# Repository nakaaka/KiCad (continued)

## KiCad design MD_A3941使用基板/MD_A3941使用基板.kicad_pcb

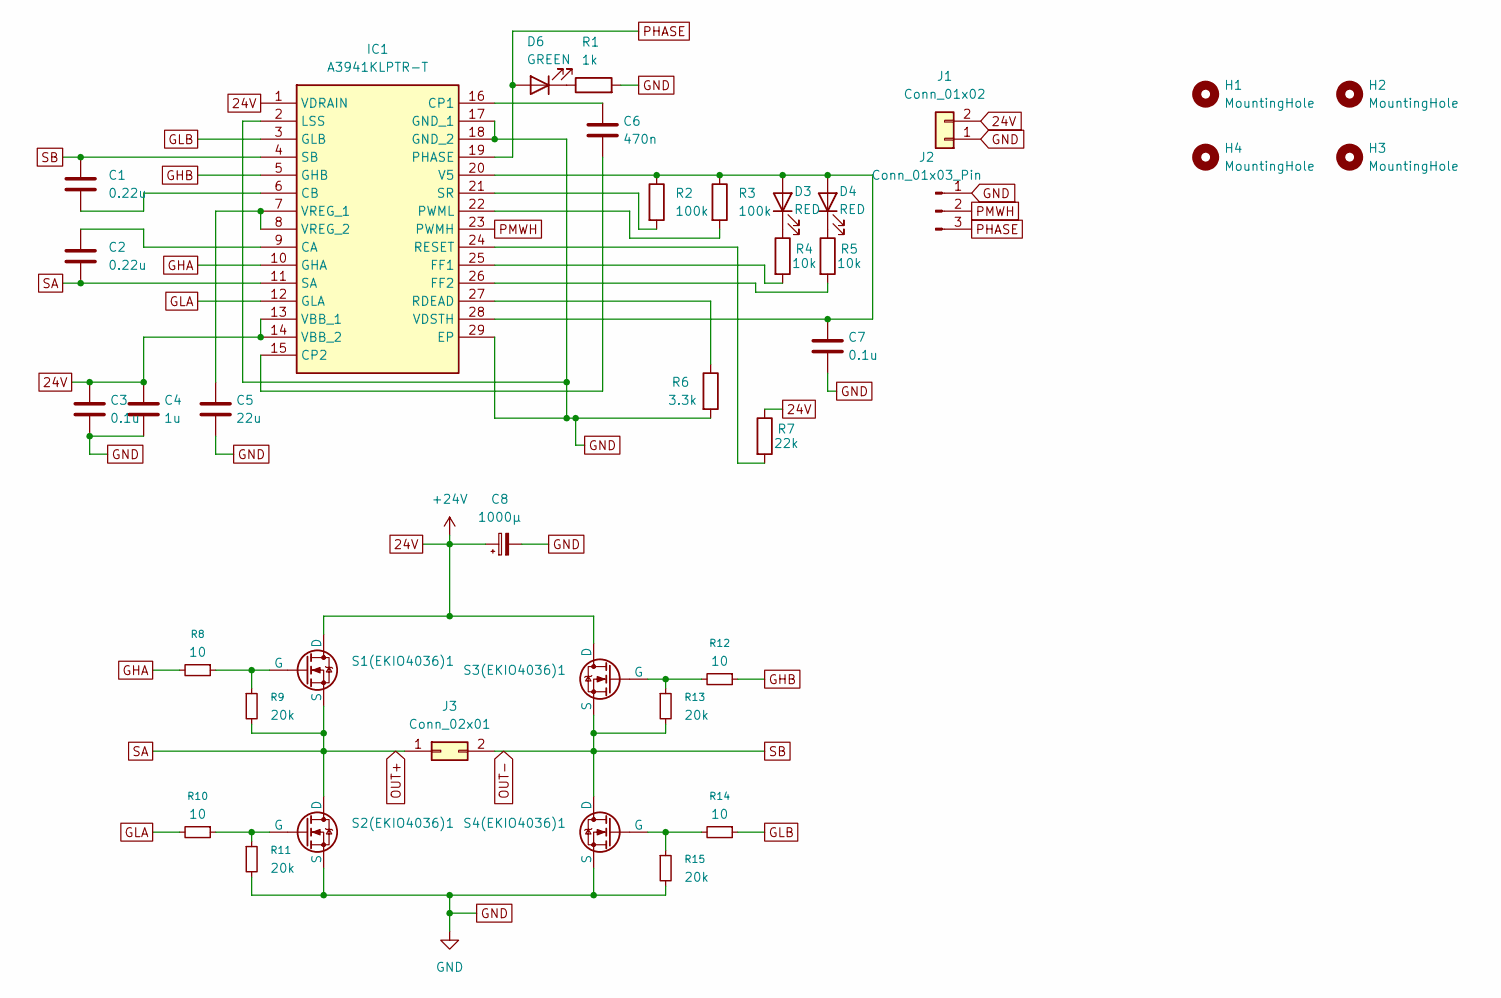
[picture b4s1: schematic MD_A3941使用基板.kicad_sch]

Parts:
C1, C2: 0.22u; C_0603_1608Metric
C3, C7: 0.1u; C_0603_1608Metric
C4: 1u; C_0603_1608Metric
C5: 22u; C_0603_1608Metric
C6: 470n; C_0603_1608Metric
C8: 1000μ; C_Radial_D12.5mm_H20.0mm_P5.00mm
D3, D4: RED; LED_0603_1608Metric
D6: GREEN; LED_0603_1608Metric
H1, H2, H3, H4: MountingHole; MountingHole_3.2mm_M3_Pad_Via
IC1: A3941KLPTR-T; A3941; Manufacturer_Part_Number A3941KLPTR-T
J1: Conn_01x02; AMASS_XT60PW-M_1x02_P7.20mm_Horizontal
J2: Conn_01x03_Pin; JST_XA_S03B-XASK-1_1x03_P2.50mm_Horizontal
J3: Conn_02x01; AMASS_XT60PW-M_1x02_P7.20mm_Horizontal
R1: 1k; R_0603_1608Metric
R2, R3: 100k; R_0603_1608Metric
R4, R5: 10k; R_0603_1608Metric
R6: 3.3k; R_0603_1608Metric
R7: 22k; R_0603_1608Metric
R8, R10, R12, R14: 10; R_0603_1608Metric
R9, R11, R13, R15: 20k; R_0603_1608Metric
S1(EKIO4036)1, S2(EKIO4036)1, S3(EKIO4036)1, S4(EKIO4036)1: NMOS; TO-220-3_Horizontal_TabUp

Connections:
24V: C3.1, C4.1, C8.1, IC1.1 (VDRAIN), IC1.13 (VBB_1), IC1.14 (VBB_2), J1.2, R7.1, S1(EKIO4036)1.1 (D), S3(EKIO4036)1.1 (D)
GHA: IC1.10 (GHA), R8.2
GHB: IC1.5 (GHB), R12.1
GLA: IC1.12 (GLA), R10.2
GLB: IC1.3 (GLB), R14.1
GND: C3.2, C4.2, C5.2, C7.2, C8.2, IC1.2 (LSS), IC1.17 (GND_1), IC1.18 (GND_2), IC1.29 (EP), J1.1, J2.1, R1.2, R6.2, R11.2, R15.2, S2(EKIO4036)1.3 (S), S4(EKIO4036)1.3 (S)
unnamed: C7.1, D3.2 (A), D4.2 (A), IC1.20 (V5), IC1.28 (VDSTH), R2.1, R3.1
unnamed: D3.1 (K), R4.1
unnamed: D4.1 (K), R5.1
unnamed: D6.1 (K), R1.1
unnamed: C2.1, IC1.9 (CA)
unnamed: C1.2, IC1.6 (CB)
unnamed: C6.1, IC1.16 (CP1)
unnamed: C6.2, IC1.15 (CP2)
unnamed: IC1.25 (FF1), R4.2
unnamed: IC1.26 (FF2), R5.2
unnamed: IC1.22 (PWML), R3.2
unnamed: IC1.27 (RDEAD), R6.1
unnamed: IC1.24 (RESET), R7.2
unnamed: IC1.21 (SR), R2.2
unnamed: C5.1, IC1.7 (VREG_1), IC1.8 (VREG_2)
unnamed: R8.1, R9.1, S1(EKIO4036)1.2 (G)
unnamed: R10.1, R11.1, S2(EKIO4036)1.2 (G)
unnamed: R12.2, R13.1, S3(EKIO4036)1.2 (G)
unnamed: R14.2, R15.1, S4(EKIO4036)1.2 (G)
OUT+: C2.2, IC1.11 (SA), J3.1, R9.2, S1(EKIO4036)1.3 (S), S2(EKIO4036)1.1 (D)
OUT-: C1.1, IC1.4 (SB), J3.2, R13.2, S3(EKIO4036)1.3 (S), S4(EKIO4036)1.1 (D)
PHASE: D6.2 (A), IC1.19 (PHASE), J2.3
PMWH: IC1.23 (PWMH), J2.2

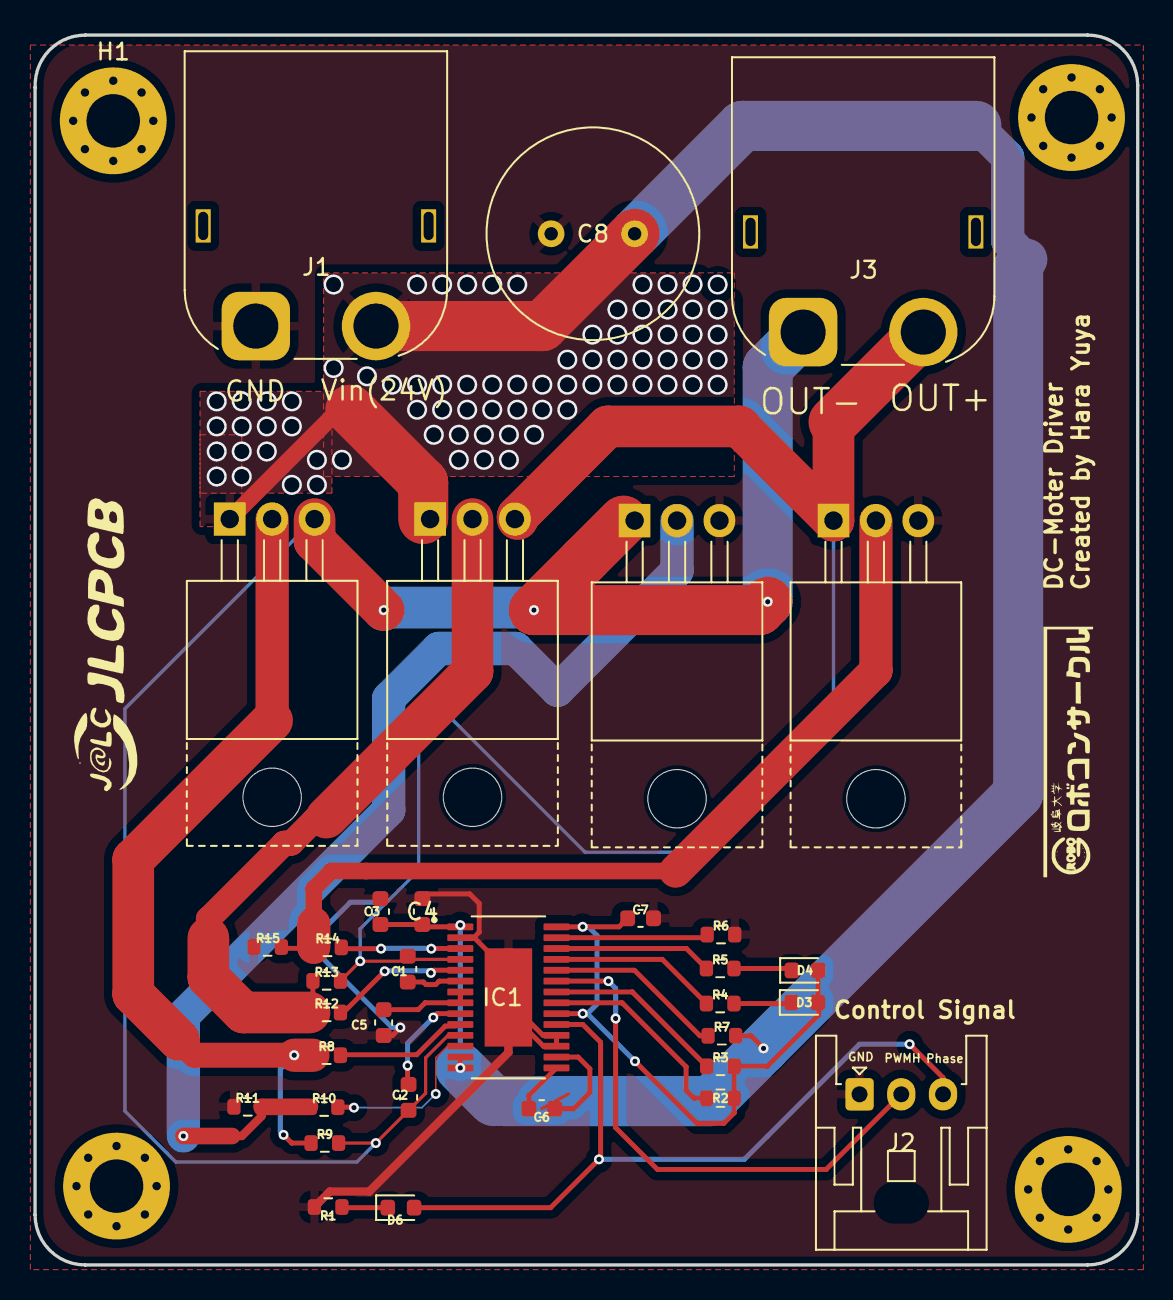
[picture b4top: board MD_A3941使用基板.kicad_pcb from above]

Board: 2 copper layers, 66.0 x 73.7 mm, 38 parts (0 on the bottom side), 29 nets.

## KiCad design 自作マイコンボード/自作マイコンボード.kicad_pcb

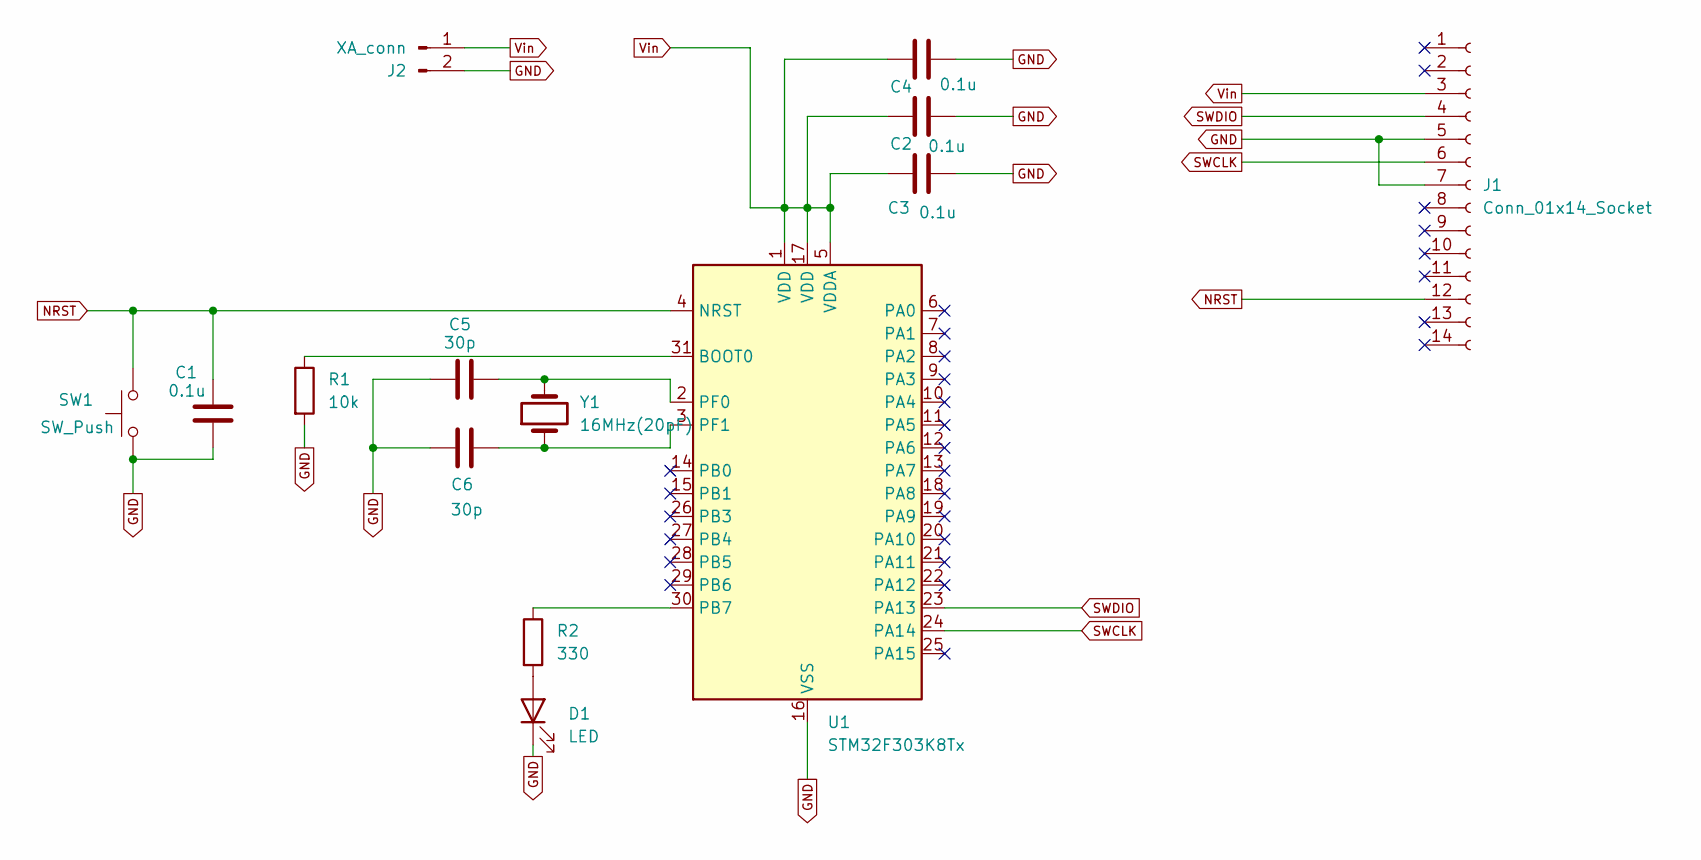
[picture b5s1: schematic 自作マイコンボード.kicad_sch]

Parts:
C1, C2, C3, C4: 0.1u; C_0603_1608Metric
C5, C6: 30p; C_0603_1608Metric
D1: LED; LED_0603_1608Metric
J1: Conn_01x14_Socket; 14pinコネクタ
J2: XA_conn; 2pinコネクタ
R1: 10k; R_0603_1608Metric
R2: 330; R_0603_1608Metric
SW1: SW_Push; SW_PUSH_6mm_H5mm
U1: STM32F303K8Tx; LQFP-32_7x7mm_P0.8mm
Y1: 16MHz(20pF); Crystal_HC49-4H_Vertical

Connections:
GND: C1.2, C2.2, C3.2, C4.2, C5.1, C6.1, D1.1 (K), J1.5, J1.7, J2.2, R1.2, SW1.1, U1.16 (VSS), U1.32 (VSS)
NRST: C1.1, J1.12, SW1.2, U1.4 (NRST)
unnamed: D1.2 (A), R2.2
unnamed: R1.1, U1.31 (BOOT0)
unnamed: R2.1, U1.30 (PB7)
unnamed: C5.2, U1.2 (PF0), Y1.2
unnamed: C6.2, U1.3 (PF1), Y1.1
SWCLK: J1.6, U1.24 (PA14)
SWDIO: J1.4, U1.23 (PA13)
Vin: C2.1, C3.1, C4.1, J1.3, J2.1, U1.1 (VDD), U1.5 (VDDA), U1.17 (VDD)

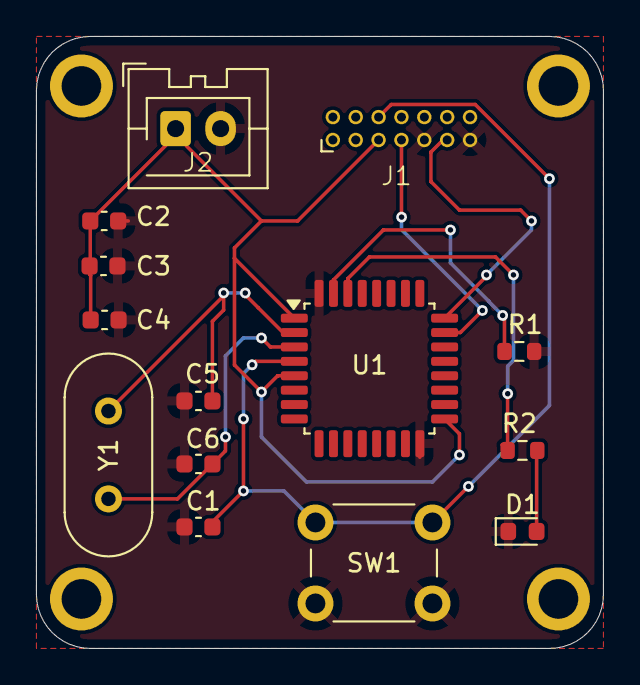
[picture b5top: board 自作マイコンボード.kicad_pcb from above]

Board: 2 copper layers, 31.5 x 34.0 mm, 14 parts (0 on the bottom side), 10 nets.

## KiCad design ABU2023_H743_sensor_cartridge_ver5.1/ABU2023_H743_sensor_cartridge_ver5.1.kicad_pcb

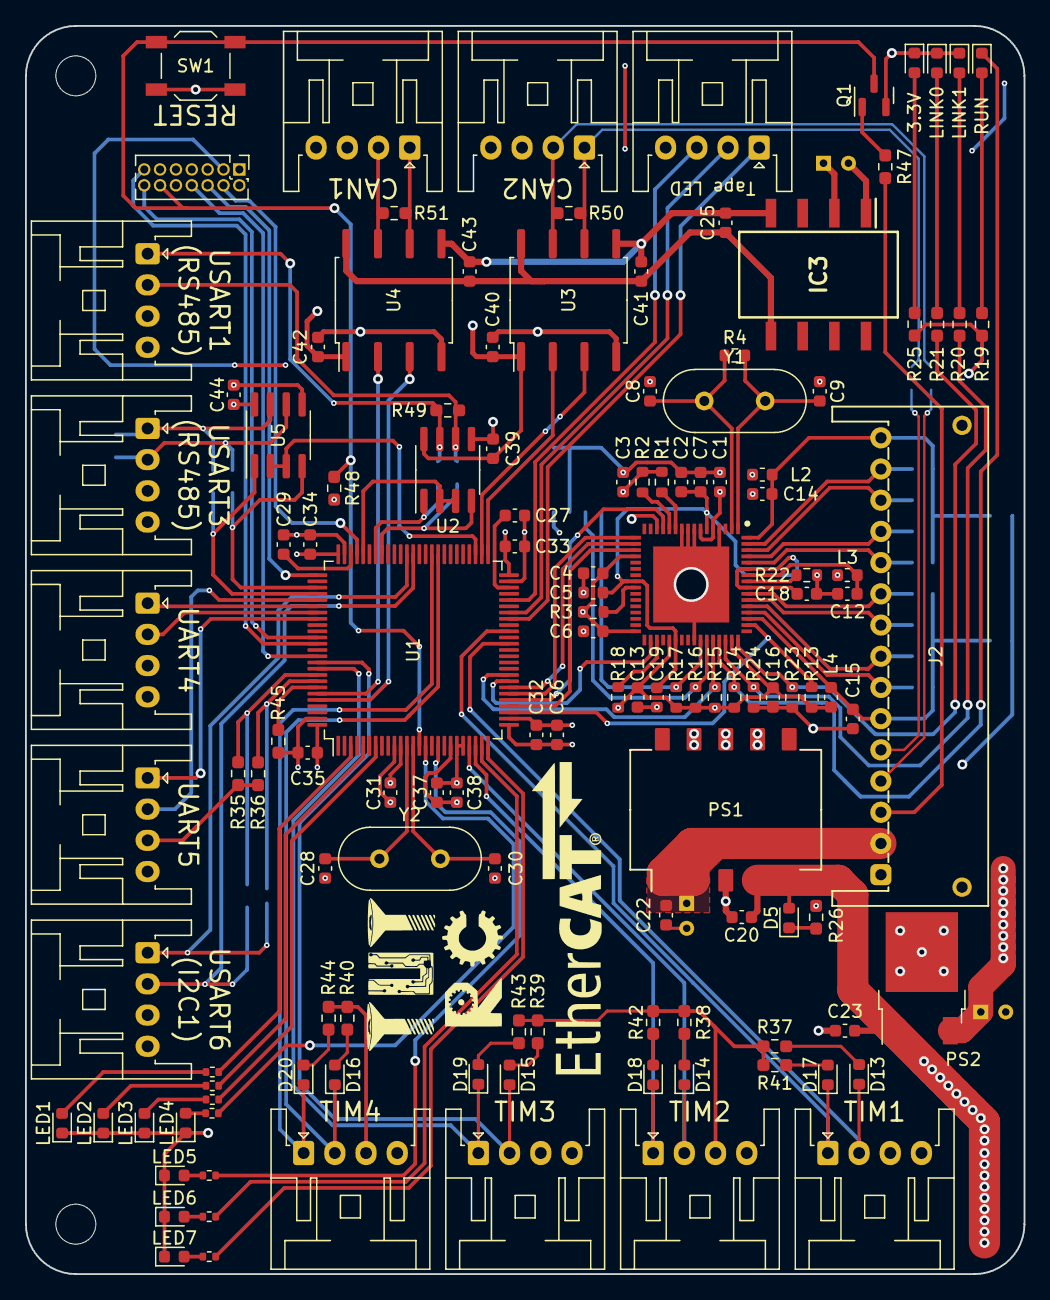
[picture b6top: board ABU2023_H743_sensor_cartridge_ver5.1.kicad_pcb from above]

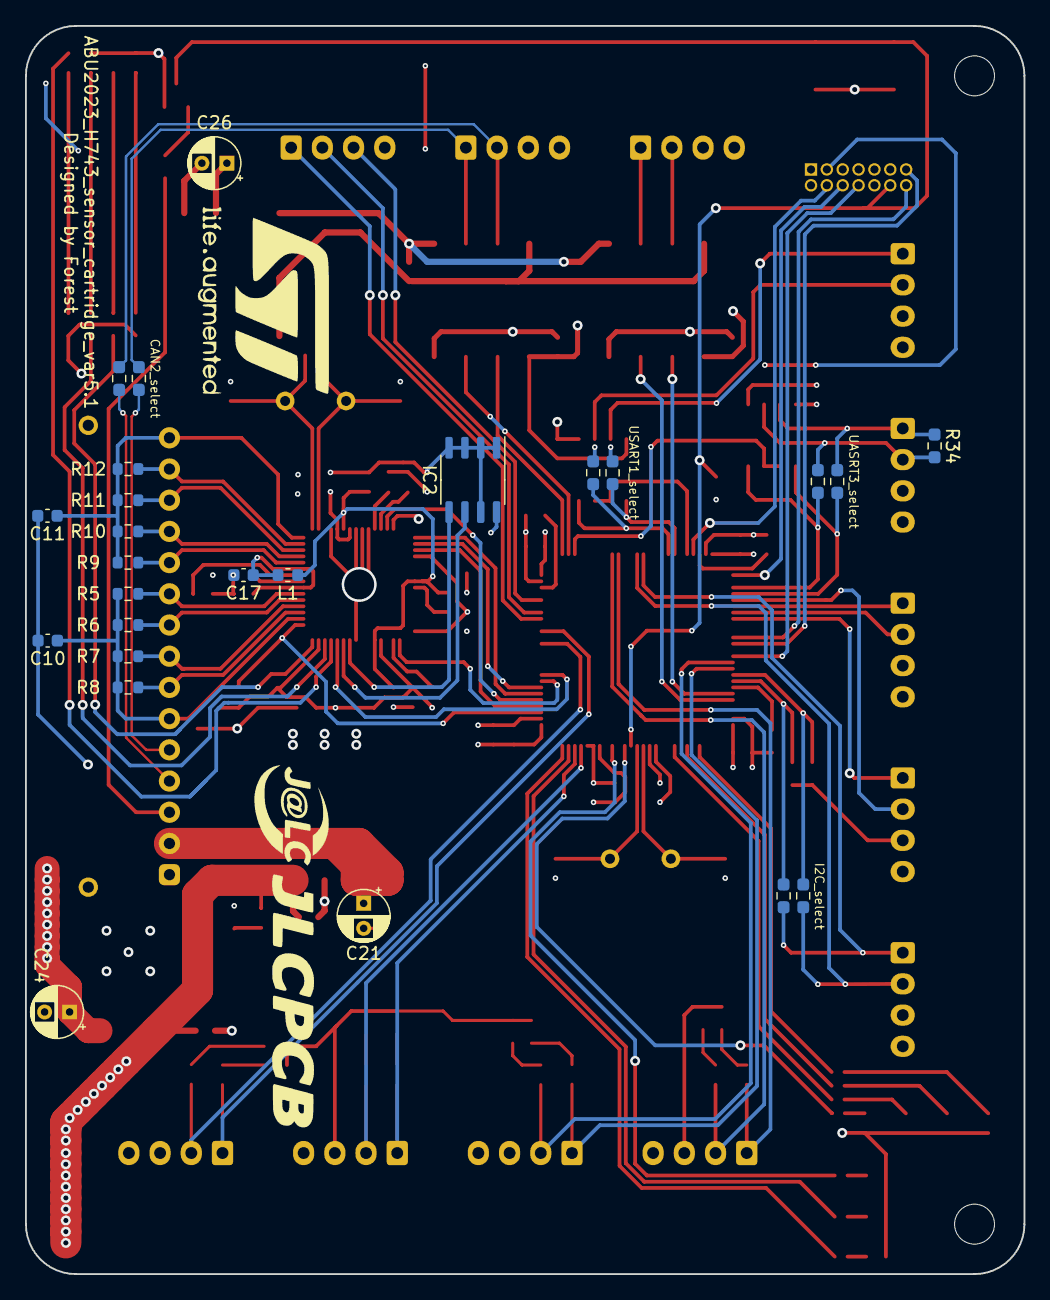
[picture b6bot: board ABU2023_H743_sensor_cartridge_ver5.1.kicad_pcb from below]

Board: 4 copper layers, 80.0 x 100.0 mm, 156 parts (25 on the bottom side), 117 nets.

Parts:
C1, C3, C4, C5, C6, C12, C13, C14, C15, C16, C17, C18, C19, C23, C31, C32, C33, C34, C35, C37, C39, C40, C41, C42, C43, C44: 0.1u; C_0603_1608Metric
C2: 420p; C_0603_1608Metric
C7, C38: 1u; C_0603_1608Metric
C8, C9: 33p; C_0603_1608Metric
C10, C11: 0,022u; C_0603_1608Metric
C20, C25, C36: 4.7u; C_0603_1608Metric
C21, C24: 47u; CP_Radial_D4.0mm_P2.00mm
C22, C27, C29: 2.2u; C_0603_1608Metric
C26: 4.7u; CP_Radial_D4.0mm_P2.00mm
C28, C30: 18p; C_0603_1608Metric
D1: RUNLED; LED_0603_1608Metric
D2: LINK1; LED_0603_1608Metric
D3: LINK0; LED_0603_1608Metric
D4: 3.3V; LED_0603_1608Metric
D5: 5V; LED_0603_1608Metric
D6, D7, D8, D9, D10, D11, D12: LED; LED_0603_1608Metric
D13, D14, D15, D16: LED_A; LED_0603_1608Metric
D17, D18, D19, D20: LED_B; LED_0603_1608Metric
IC1: LAN9253; QFN50P900X900X100-65N-D
IC2: 24FC512-I_P; SO-8_3.9x4.9mm_P1.27mm
IC3: VBT1-S5-S5-SMT; SOP254P1120X625-8N
J1: USART6; JST_XA_S04B-XASK-1_1x04_P2.50mm_Horizontal
J2: JL_01x15; JST_JL_S15B-JL-R
J3: UART4; JST_XA_S04B-XASK-1_1x04_P2.50mm_Horizontal
J4: UART5; JST_XA_S04B-XASK-1_1x04_P2.50mm_Horizontal
J5: UART3; JST_XA_S04B-XASK-1_1x04_P2.50mm_Horizontal
J6: UART1; JST_XA_S04B-XASK-1_1x04_P2.50mm_Horizontal
J7: CAN1; JST_XA_S04B-XASK-1_1x04_P2.50mm_Horizontal
J8: CAN2; JST_XA_S04B-XASK-1_1x04_P2.50mm_Horizontal
J9, J10, J11, J12: IncEncoder; JST_XA_S04B-XASK-1_1x04_P2.50mm_Horizontal
J13: TapeLED; JST_XA_S04B-XASK-1_1x04_P2.50mm_Horizontal
J14: STLINK-V3; STLINK-V3_THT
JP1, JP2, JP3, JP4, JP5, JP6, JP7, JP8: Jumper; R_0603_1608Metric_Pad0.98x0.95mm_HandSolder
L1, L2, L3, L4: 10m; L_0603_1608Metric
PS1: M78SAR05-0.5; M78SAR
PS2: NJM2391DL1-33; TO-252-2
Q1: 2N7002; SOT-23
R1, R2, R3, R13, R14, R15, R16, R17, R18, R23, R24: 4.7k; R_0603_1608Metric
R4: 1M; R_0603_1608Metric
R5, R6, R7, R8, R9, R10, R11, R12: 49.9; R_0603_1608Metric
R19, R20, R21, R25, R26, R35, R36, R37, R38, R39, R40, R41, R42, R43, R44, R48: 4.7k; R_0603_1608Metric_Pad0.98x0.95mm_HandSolder
R22: 12.1k; R_0603_1608Metric
R27, R28, R29, R30, R31, R32, R33: 4.7k; R_0402_1005Metric
R34, R49, R50, R51: 120; R_0603_1608Metric_Pad0.98x0.95mm_HandSolder
R45: 10k; R_0603_1608Metric_Pad0.98x0.95mm_HandSolder
R47: 1k; R_0603_1608Metric_Pad0.98x0.95mm_HandSolder
REF1, REF1#2: MountingHole_3.2mm_M3
SW1: SW_Push; SW_SPST_TL3342
U1: STM32H743VITx; LQFP-100_14x14mm_P0.5mm
U2, U5: MAX485E; SOIC-8_3.9x4.9mm_P1.27mm
U3, U4: ISO1050DUB; SOP-8_6.62x9.15mm_P2.54mm
Y1: 25MHz; Crystal_HC49-4H_Vertical
Y2: 32MHz; Crystal_HC49-4H_Vertical

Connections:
+1V2: C2.2, C5.2, C7.2, C19.1, IC1.6 (VDDCR_1), IC1.24 (VDDCR_2), IC1.38 (VDDCR_3), L1.1
+3V3: C1.2, C3.1, C4.2, C6.2, C13.1, C16.1, C24.1, C31.1, C32.1, C33.1, C34.1, C35.1, C36.1, C37.1, C38.1, IC1.5 (VDD33), IC1.7 (REG_EN), IC1.14 (VDDIO_1), IC1.20 (VDDIO_2), IC1.32 (VDDIO_3), IC1.37 (VDDIO_4), IC1.47 (VDDIO_5), IC2.8 (VCC), J14.3 (VDD), L2.1, L3.1, L4.1, PS2.3 (VOUT), R1.1, R2.1, R3.1, R13.2, R14.2, R15.2, R16.2, R17.2, R18.2, R19.1, R25.1, R48.1, U1.11 (VDD), U1.20 (VREF+), U1.21 (VDDA), U1.27 (VDD), U1.50 (VDD), U1.75 (VDD), U1.100 (VDD)
+5V: C20.1, C23.1, C26.1, C39.1, C40.2, C42.2, C44.1, D5.2 (A), IC3.2 (+VIN), J1.3, J3.3, J4.3, J5.3, J6.3, J9.3, J10.3, J11.3, J12.3, PS1.4 (Vout), PS1.5 (Vout), PS2.1 (VIN), R35.2, R36.2, R37.2, R38.2, R39.2, R40.2, R41.2, R42.2, R43.2, R44.2, U2.8 (VCC), U3.1 (VCC1), U4.1 (VCC1), U5.8 (VCC)
+5VA: C25.1, C41.2, C43.2, IC3.5 (+VO), U3.8 (VCC2), U4.8 (VCC2)
+12V: C21.1, C22.2, J2.2, J7.3, J8.3, PS1.1 (Vin), PS1.2 (Vin)
/CAN1_RX: U1.95 (PB8), U4.2 (RXD)
/CAN1_TX: U1.96 (PB9), U4.3 (TXD)
/CAN2_N: J8.1, JP7.2 (B), R50.2, U3.6 (CANL)
/CAN2_P: J8.2, JP8.2 (B), R50.1, U3.7 (CANH)
/CAN2_RX: U1.51 (PB12), U3.2 (RXD)
/CAN2_TX: U1.52 (PB13), U3.3 (TXD)
/I2C1_SCL: JP4.1 (A), R35.1, U1.92 (PB6)
/I2C1_SDA: JP3.1 (A), R36.1, U1.93 (PB7)
/IRQ: IC1.44 (IRQ/LATCH1), R15.1, U1.34 (PB0)
/ISO1050_1/CAN_H: J7.2, R51.1, U4.7 (CANH)
/ISO1050_1/CAN_L: J7.1, R51.2, U4.6 (CANL)
/LAN9253/RST#: IC1.11 (RST#), R1.2
/LAN9253/SCL: IC1.43 (EESCL/TCK/EE_EMUL2), IC2.6 (SCL), R16.1
/LAN9253/SDA: IC1.42 (EESDA/TMS/EE_EMUL1), IC2.5 (SDA), R17.1
/LAN9253/SIO2: IC1.12 (D2/AD2/SOF/SIO2/EE_EMUL_SPI0), R2.2
/LAN9253/SIO3: IC1.35 (D3/AD3/WD_TRIG/SIO3/EE_EMUL_SPI1), R18.1
/LED1: R27.1, U1.3 (PE4)
/LED2: R28.1, U1.5 (PE6)
/LED3: R29.1, U1.7 (PC13)
/LED4: R30.1, U1.15 (PC0)
/LED5: R31.1, U1.17 (PC2_C)
/LED6: R32.1, U1.24 (PA2)
/LED7: R33.1, U1.25 (PA3)
/LINKLED0: IC1.46 (LINKACTLED1/TDI/CHIP_MODE1/LEDPOL1), R20.1, R24.1
/LINKLED1: IC1.48 (LINKACTLED0/TDO/CHIP_MODE0/100FD_A/LEDP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), R21.1, R23.1
/MAX485E_1/A: J5.2, JP6.2 (B), R34.2, U5.6 (A)
/MAX485E_1/B: J5.1, JP5.2 (B), R34.1, U5.7 (B)
/MAX485E_2/A: J6.2, JP2.2 (B), R49.2, U2.6 (A)
/MAX485E_2/B: J6.1, JP1.2 (B), R49.1, U2.7 (B)
/RESET: J2.3, R47.1
/RUNLED: D1.1 (K), IC1.45 (RUNLED/STATE_RUNLED/E2PSIZE/EE_EMUL0/LE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), R14.1
/RXAN: IC1.54 (RXNA), J2.9, R6.2
/RXAP: IC1.55 (RXPA), J2.10, R5.1
/RXBN: IC1.61 (RXNB), J2.12, R10.2
/RXBP: IC1.60 (RXPB), J2.11, R9.1
/SCK: IC1.19 (D9/AD9/LATCH_IN/SCK), U1.29 (PA5)
/SIO0: IC1.17 (D0/AD0/WD_STATE/SI/SIO0), U1.31 (PA7)
/SIO1: IC1.13 (D1/AD1/EOF/SO/SIO1), U1.30 (PA6)
/SS: IC1.50 (D5/AD5/OUTVALID/SCS#), R13.1, U1.28 (PA4)
/STM32H743VGT6/NRST: J14.12 (NRST), Q1.3 (D), R48.2, SW1.2, U1.14 (NRST)
/STM32H743VGT6/SWCLK: J14.6 (SWCLK), U1.76 (PA14)
/STM32H743VGT6/SWDIO: J14.4 (SWDIO), U1.72 (PA13)
/STM32H743VGT6/SWO: J14.8 (SWO), U1.89 (PB3)
/STM32H743VGT6/VCP_Target_RX: J14.13 (STLINK_TX), U1.87 (PD6)
/STM32H743VGT6/VCP_Target_TX: J14.14 (STLINK_RX), U1.86 (PD5)
/SYNC0: IC1.34 (SYNC0/LATCH0/PME), U1.33 (PC5)
/SYNC1: IC1.18 (SYNC1/LATCH1/PME), U1.32 (PC4)
/TIM1_CH1: D13.1 (K), J9.2, U1.39 (PE9)
/TIM1_CH2: D17.1 (K), J9.1, U1.41 (PE11)
/TIM2_CH1: D14.1 (K), J10.2, U1.22 (PA0)
/TIM2_CH2: D18.1 (K), J10.1, U1.23 (PA1)
/TIM3_CH1: D15.1 (K), J11.2, U1.90 (PB4)
/TIM3_CH2: D19.1 (K), J11.1, U1.91 (PB5)
/TIM4_CH1: D16.1 (K), J12.2, U1.59 (PD12)
/TIM4_CH2: D20.1 (K), J12.1, U1.60 (PD13)
/TXAN: IC1.52 (TXNA), J2.7, R8.2
/TXAP: IC1.53 (TXPA), J2.8, R7.1
/TXBN: IC1.63 (TXNB), J2.14, R12.2
/TXBP: IC1.62 (TXPB), J2.13, R11.1
/TapeLED_B: J13.3, U1.46 (PB10)
/TapeLED_G: J13.2, U1.44 (PE14)
/TapeLED_R: J13.1, U1.43 (PE13)
/UART4_RX: J3.1, U1.81 (PD0)
/UART4_TX: J3.2, U1.82 (PD1)
/UART5_RX: J4.1, U1.83 (PD2)
/UART5_TX: J4.2, U1.80 (PC12)
/USART1_DE: U1.71 (PA12), U2.2 (~RE), U2.3 (DE)
/USART1_RX: JP1.1 (A), U1.69 (PA10), U2.1 (RO)
/USART1_TX: JP2.1 (A), U1.68 (PA9), U2.4 (DI)
/USART3_DE: U1.53 (PB14), U5.2 (~RE), U5.3 (DE)
/USART3_RX: JP5.1 (A), U1.79 (PC11), U5.1 (RO)
/USART3_TX: JP6.1 (A), U1.78 (PC10), U5.4 (DI)
/USART6_RX: J1.1, JP3.2 (B), U1.64 (PC7)
/USART6_TX: J1.2, JP4.2 (B), U1.63 (PC6)
/VDD33TXRX1: C10.1, C15.1, IC1.51 (VDD33TXRX1), J2.6, L4.2, R5.2, R6.1, R7.2, R8.1
/VDD33TXRX2: C11.1, C14.1, IC1.64 (VDD33TXRX2), J2.15, L2.2, R9.2, R10.1, R11.2, R12.1
GND: C1.1, C2.1, C3.2, C4.1, C5.1, C6.1, C7.1, C8.1, C9.1, C10.2, C11.2, C12.2, C13.2, C14.2, C15.2, C16.2, C17.2, C18.2, C19.2, C20.2, C21.2, C22.1, C23.2, C24.2, C26.2, C27.2, C28.2, C29.2, C30.2, C31.2, C32.2, C33.2, C34.2, C35.2, C36.2, C37.2, C38.2, C39.2, C40.1, C42.1, C44.2, D2.1 (K), D3.1 (K), D4.1 (K), D6.1 (K), D7.1 (K), D8.1 (K), D9.1 (K), D10.1 (K), D11.1 (K), D12.1 (K), IC1.4 (OSCVSS), IC1.8 (CLK_25/CLK_25_EN/XTAL_MODE), IC1.9 (ERRLED/PME/100FD_B/LEDPOL4), IC1.10 (WAIT_ACK/PME/LATCH0//EE_EMUL_SPI3), IC1.41 (TESTMODE), IC1.65 (VSS), IC2.1 (A0), IC2.2 (A1), IC2.3 (A2), IC2.4 (VSS), IC2.7 (WP), IC3.1 (GND), J1.4, J2.1, J3.4, J4.4, J5.4, J6.4, J7.4, J8.4, J9.4, J10.4, J11.4, J12.4, J13.4, J14.5 (VSS), J14.7 (VSS), PS1.3 (GND), PS1.7 (GND), PS1.8 (GND)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
GNDA: C25.2, C41.1, C43.1, IC3.4 (0_V), U3.5 (GND2), U4.5 (GND2)
unnamed: D1.2 (A), R19.2
unnamed: D2.2 (A), R20.2
unnamed: D3.2 (A), R21.2
unnamed: D4.2 (A), R25.2
unnamed: D5.1 (K), R26.1
unnamed: D6.2 (A), R27.2
unnamed: D7.2 (A), R28.2
unnamed: D8.2 (A), R29.2
unnamed: D9.2 (A), R30.2
unnamed: D10.2 (A), R31.2
unnamed: D11.2 (A), R32.2
unnamed: D12.2 (A), R33.2
unnamed: D13.2 (A), R37.1
unnamed: D14.2 (A), R38.1
unnamed: D15.2 (A), R39.1
unnamed: D16.2 (A), R40.1
unnamed: D17.2 (A), R41.1
unnamed: D18.2 (A), R42.1
unnamed: D19.2 (A), R43.1
unnamed: D20.2 (A), R44.1
unnamed: IC1.25 (A1/ALELO/OE_EXT/MII_CLK25//EE_EMUL_SPI2), R3.2
unnamed: C9.2, IC1.1 (OSCI), R4.2, Y1.2
unnamed: C8.2, IC1.2 (OSCO), R4.1, Y1.1
unnamed: IC1.57 (RBIAS), R22.1
unnamed: C17.1, C18.1, IC1.56 (VDD12TX1), IC1.59 (VDD12TX2), L1.2
unnamed: C12.1, IC1.58 (VDD33BIAS), L3.2
unnamed: J2.4, JP8.1 (A)
unnamed: J2.5, JP7.1 (A)
unnamed: Q1.1 (G), R47.2
unnamed: R45.2, U1.94 (BOOT0)
unnamed: C28.1, U1.12 (PH0), Y2.1
unnamed: C30.1, U1.13 (PH1), Y2.2
unnamed: C27.1, U1.48 (VCAP1)
unnamed: C29.1, U1.73 (VCAP2)

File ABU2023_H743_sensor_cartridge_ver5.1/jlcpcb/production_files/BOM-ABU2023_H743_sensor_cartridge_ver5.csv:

Comment,Designator,Footprint,LCSC
STM32H743VITx,U1,LQFP-100_14x14mm_P0.5mm,C114409
0.1u,"C1,C12,C13,C14,C15,C16,C17,C18,C19,C23,C3,C31,C32,C33,C34,C35,C37,C39,C4,C40,C41,C42,C43,C44,C5,C6",C_0603_1608Metric,C14663
1u,"C38,C7",C_0603_1608Metric,C15849
ISO1050DUB,"U3,U4",SOP-8_6.62x9.15mm_P2.54mm,C16428
18p,"C28,C30",C_0603_1608Metric,C1647
33p,"C8,C9",C_0603_1608Metric,C1663
4.7u,"C20,C25,C36",C_0603_1608Metric,C19666
"0,022u","C10,C11",C_0603_1608Metric,C21122
1k,R47,R_0603_1608Metric_Pad0.98x0.95mm_HandSolder,C21190
120,"R34,R49,R50,R51",R_0603_1608Metric_Pad0.98x0.95mm_HandSolder,C22787
5V,D5,LED_0603_1608Metric,C2286
LED,"D11,D7,D9",LED_0603_1608Metric,C2290
1M,R4,R_0603_1608Metric,C22935
4.7k,"R1,R13,R14,R15,R16,R17,R18,R19,R2,R20,R21,R23,R24,R25,R26,R3,R35,R36,R37,R38,R39,R40,R41,R42,R43,R44,R48",R_0603_1608Metric,C23162
49.9,"R10,R11,R12,R5,R6,R7,R8,R9",R_0603_1608Metric,C23185
2.2u,"C22,C27,C29",C_0603_1608Metric,C23630
10k,R45,R_0603_1608Metric_Pad0.98x0.95mm_HandSolder,C25804
4.7k,"R27,R28,R29,R30,R31,R32,R33",R_0402_1005Metric,C25900
USART6,"J1,J10,J11,J12,J13,J3,J4,J5,J6,J7,J8,J9",JST_XA_S04B-XASK-1_1x04_P2.50mm_Horizontal,C265097
SW_Push,SW1,SW_SPST_TL3342,C318884
MAX485E,"U2,U5",SOIC-8_3.9x4.9mm_P1.27mm,C6855
12.1k,R22,R_0603_1608Metric,C705893
RUNLED,"D1,D10,D12,D6,D8",LED_0603_1608Metric,C72038
LED_B,"D17,D18,D19,D2,D20,D3",LED_0603_1608Metric,C72041
LED_A,"D13,D14,D15,D16,D4",LED_0603_1608Metric,C72043
2N7002,Q1,SOT-23,C8545
10m,"L1,L2,L3,L4",L_0603_1608Metric,C85827
Jumper,JP6,R_0603_1608Metric_Pad0.98x0.95mm_HandSolder,
Jumper,JP8,R_0603_1608Metric_Pad0.98x0.95mm_HandSolder,
Jumper,JP7,R_0603_1608Metric_Pad0.98x0.95mm_HandSolder,
Jumper,JP5,R_0603_1608Metric_Pad0.98x0.95mm_HandSolder,
Jumper,JP4,R_0603_1608Metric_Pad0.98x0.95mm_HandSolder,
Jumper,JP3,R_0603_1608Metric_Pad0.98x0.95mm_HandSolder,
Jumper,JP2,R_0603_1608Metric_Pad0.98x0.95mm_HandSolder,
Jumper,JP1,R_0603_1608Metric_Pad0.98x0.95mm_HandSolder,
32MHz,Y2,Crystal_HC49-4H_Vertical,
M78SAR05-0.5,PS1,M78SAR,
NJM2391DL1-33,PS2,TO-252-2,
420p,C2,C_0603_1608Metric,
25MHz,Y1,Crystal_HC49-4H_Vertical,
JL_01x15,J2,JST_JL_S15B-JL-R,
STLINK-V3,J14,STLINK-V3_THT,
VBT1-S5-S5-SMT,IC3,SOP254P1120X625-8N,
LAN9253,IC1,QFN50P900X900X100-65N-D,
47u,C24,CP_Radial_D4.0mm_P2.00mm,
47u,C21,CP_Radial_D4.0mm_P2.00mm,
24FC512-I_P,IC2,SO-8_3.9x4.9mm_P1.27mm,
4.7u,C26,CP_Radial_D4.0mm_P2.00mm,

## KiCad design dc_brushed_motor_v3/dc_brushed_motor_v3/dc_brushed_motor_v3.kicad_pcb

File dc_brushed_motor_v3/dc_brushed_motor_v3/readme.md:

ブラシ付きモータードライバーの制作
堀江　新

回路設計は原と堀江で行った。

---- メモ ----
mosfetは複数の企業が販売しているが、大きさは規格化されている。(例　TO220)
　　(レギュレータなども同規格で表されることが多い)

表面実装はSMD、スルーホールはTHTで表される

スルーホールの部品の足を切って、基盤に表面実装することをリードフォーミングという
stagger_odd とstagger_evenについて
　　リードの曲げ方。
　　stagger_oddは奇数を曲げる
　　stagger_evenは偶数番目で曲げる
　　ショートしにくいのはstagger_even

基本的に、スルーホールのfetであれば、リードにはんだ付けする
タブはドレインになっていることが多いが、放熱用なので、基盤にねじ固定することが主流

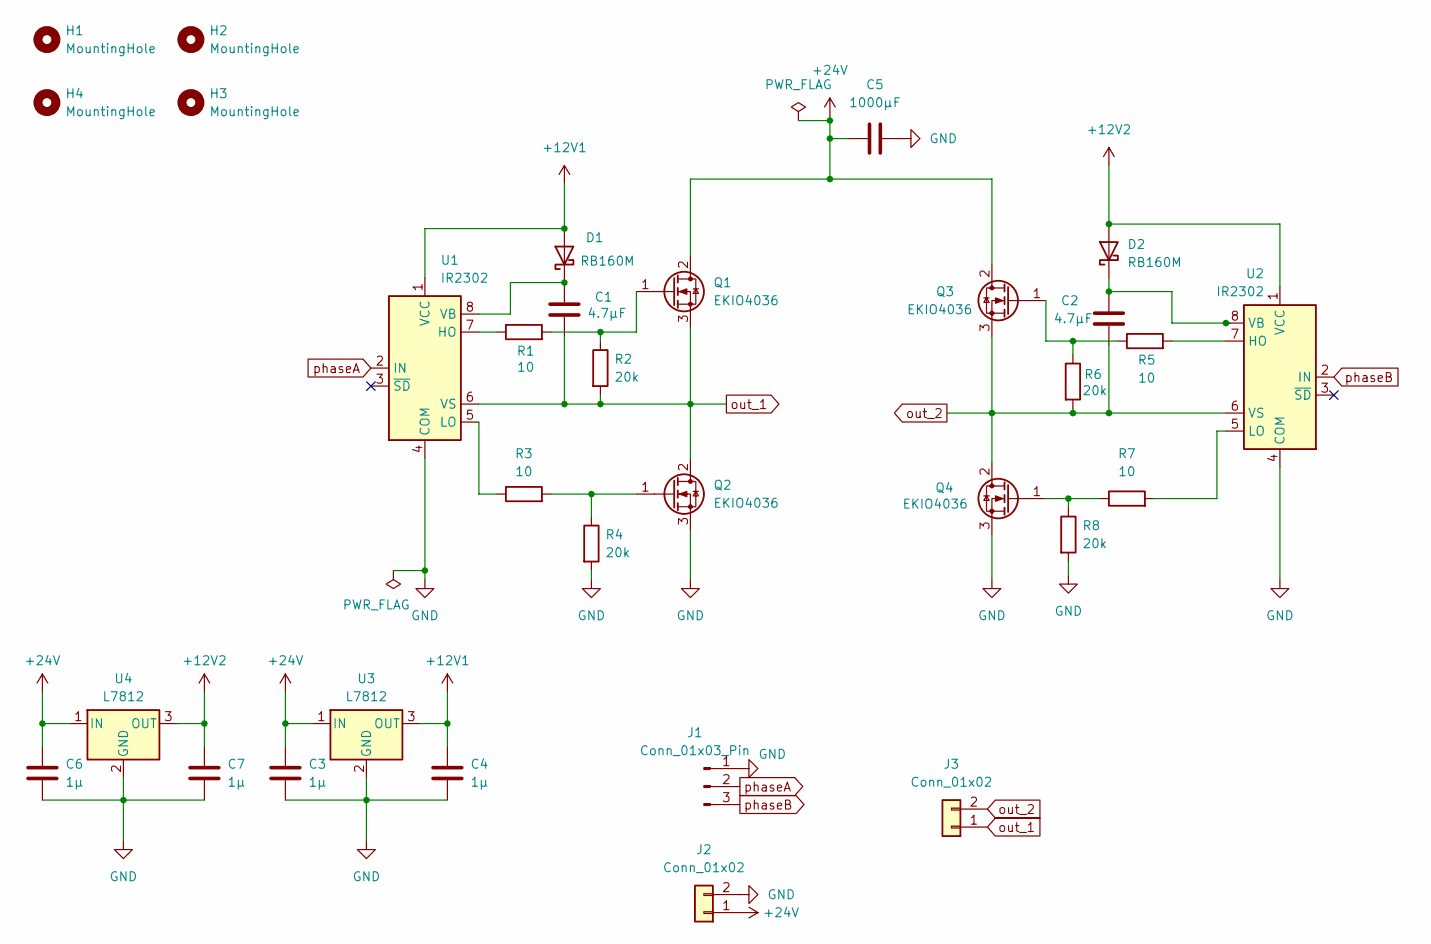
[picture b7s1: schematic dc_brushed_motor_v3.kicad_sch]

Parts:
C1, C2: 4.7μF; C_0603_1608Metric_Pad1.08x0.95mm_HandSolder
C3, C4, C6, C7: 1μ; C_0603_1608Metric_Pad1.08x0.95mm_HandSolder
C5: 1000μF; C_Radial_D12.5mm_H20.0mm_P5.00mm
D1, D2: RB160M; rb160m
H1, H2, H3, H4: MountingHole; MountingHole_3.2mm_M3_Pad_Via
J1: Conn_01x03_Pin; JST_XA_S03B-XASK-1_1x03_P2.50mm_Horizontal
J2, J3: Conn_01x02; AMASS_XT60PW-M_1x02_P7.20mm_Horizontal
Q1, Q2, Q3, Q4: EKIO4036; TO-220-2_Horizontal_TabDown
R1, R3, R5, R7: 10; R_0603_1608Metric_Pad0.98x0.95mm_HandSolder
R2, R4, R6, R8: 20k; R_0603_1608Metric_Pad0.98x0.95mm_HandSolder
U1, U2: IR2302; SOIC-8_3.9x4.9mm_P1.27mm
U3, U4: L7812; TO-220-3_Horizontal_TabUp

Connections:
+12V1: C4.1, D1.2 (A), U1.1 (VCC), U3.3 (OUT)
+12V2: C7.1, D2.2 (A), U2.1 (VCC), U4.3 (OUT)
+24V: C3.1, C5.1, C6.1, J2.1, Q1.2 (D), Q3.2 (D), U3.1 (IN), U4.1 (IN)
GND: C3.2, C4.2, C5.2, C6.2, C7.2, J1.1, J2.2, Q2.3 (S), Q4.3 (S), R4.2, R8.2, U1.4 (COM), U2.4 (COM), U3.2 (GND), U4.2 (GND)
unnamed: C1.1, D1.1 (K), U1.8 (VB)
unnamed: C2.1, D2.1 (K), U2.8 (VB)
unnamed: Q1.1 (G), R1.2, R2.1
unnamed: Q2.1 (G), R3.2, R4.1
unnamed: Q3.1 (G), R5.1, R6.1
unnamed: Q4.1 (G), R7.1, R8.1
unnamed: R1.1, U1.7 (HO)
unnamed: R3.1, U1.5 (LO)
unnamed: R5.2, U2.7 (HO)
unnamed: R7.2, U2.5 (LO)
out_1: C1.2, J3.1, Q1.3 (S), Q2.2 (D), R2.2, U1.6 (VS)
out_2: C2.2, J3.2, Q3.3 (S), Q4.2 (D), R6.2, U2.6 (VS)
phaseA: J1.2, U1.2 (IN)
phaseB: J1.3, U2.2 (IN)

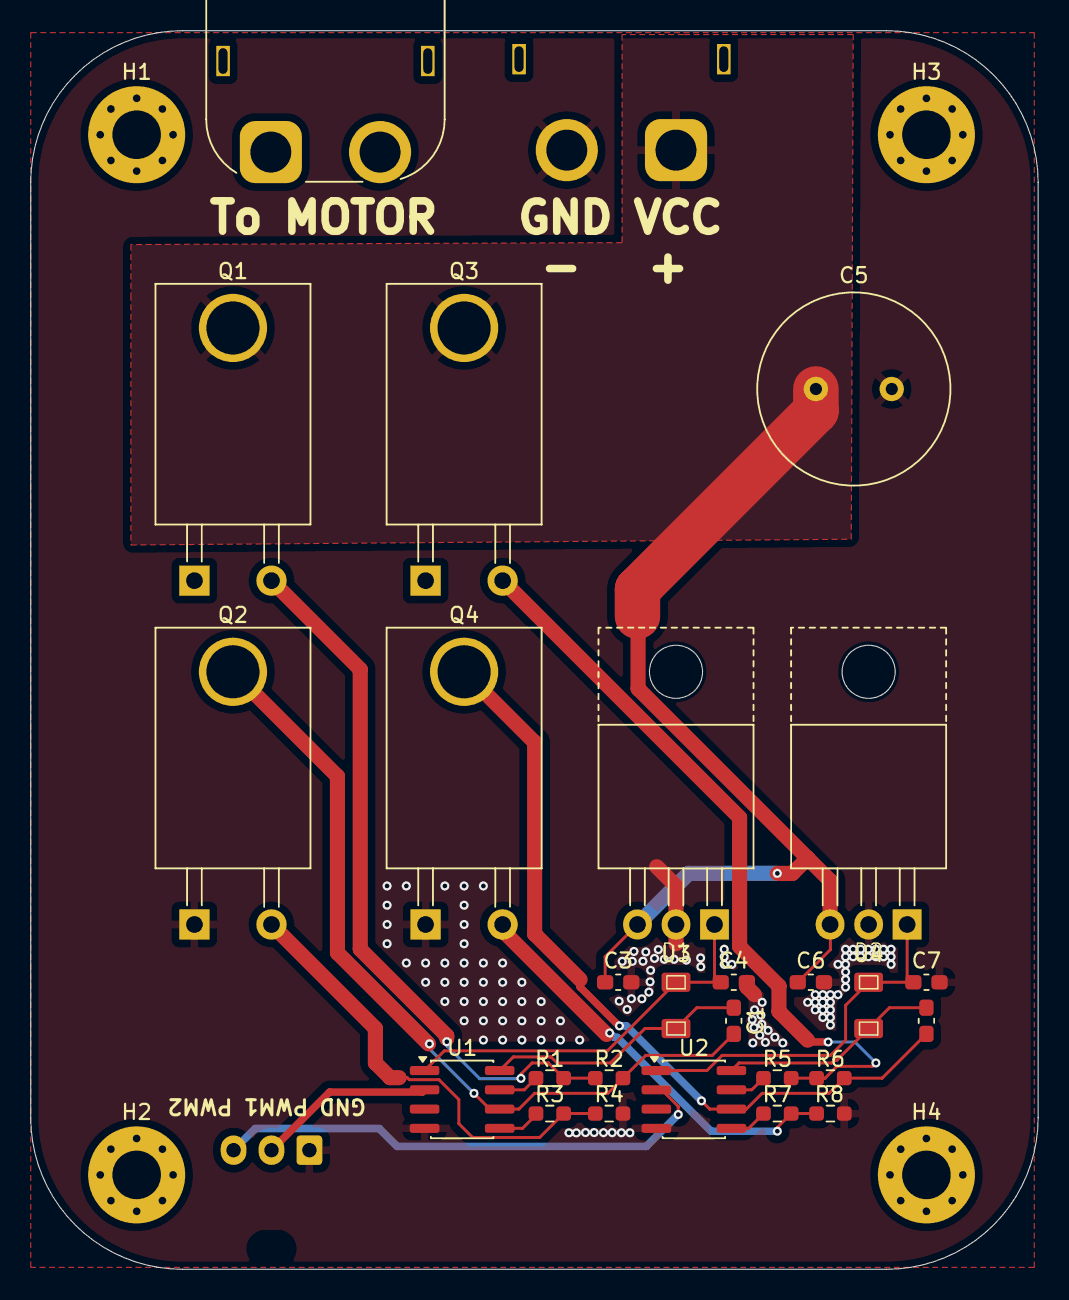
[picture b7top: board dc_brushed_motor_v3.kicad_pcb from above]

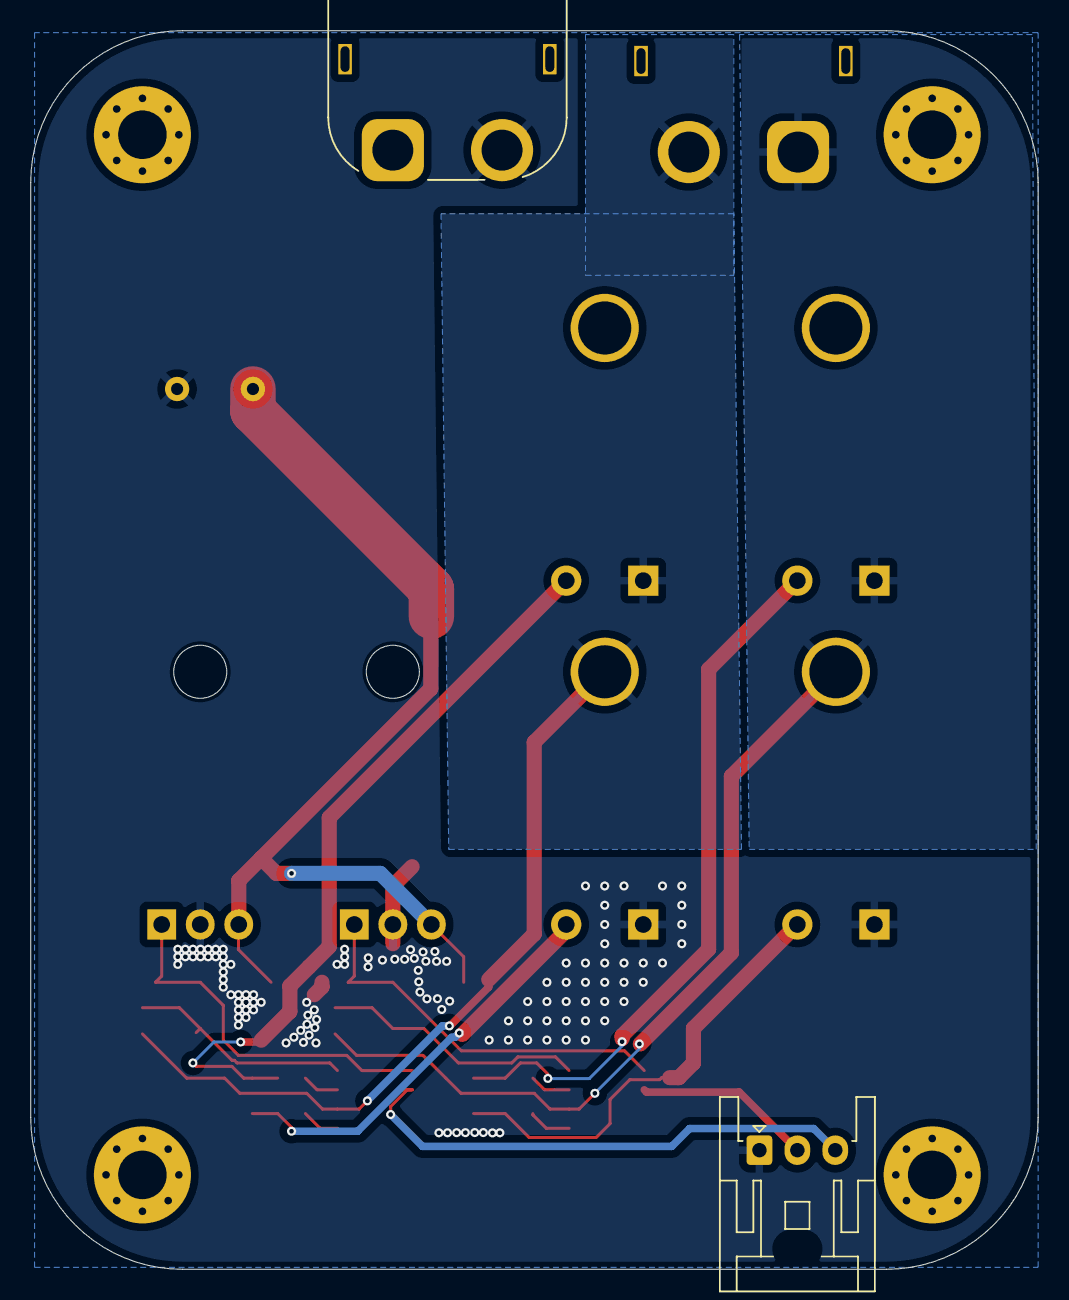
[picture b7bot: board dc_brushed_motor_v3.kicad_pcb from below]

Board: 2 copper layers, 66.4 x 81.7 mm, 32 parts (2 on the bottom side), 18 nets.

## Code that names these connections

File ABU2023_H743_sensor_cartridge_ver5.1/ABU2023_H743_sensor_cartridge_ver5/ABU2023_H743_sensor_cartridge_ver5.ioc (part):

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Mcu.Name=STM32H743VITx
Mcu.Package=LQFP100
Mcu.UserName=STM32H743VITx
PA0.Signal=S_TIM2_CH1_ETR
PA1.Signal=S_TIM2_CH2
PA10.Mode=Asynchronous
PA10.Signal=USART1_RX
PA12.Mode=Hardware Flow Control (RS485)
PA12.Signal=USART1_DE
PA13\ (JTMS/SWDIO).Mode=Trace_Asynchronous_SW
PA13\ (JTMS/SWDIO).Signal=DEBUG_JTMS-SWDIO
PA14\ (JTCK/SWCLK).Mode=Trace_Asynchronous_SW
PA14\ (JTCK/SWCLK).Signal=DEBUG_JTCK-SWCLK
PA2.GPIOParameters=GPIO_Label
PA2.GPIO_Label=LED6
PA2.Signal=GPIO_Output
PA3.GPIOParameters=GPIO_Label
PA3.GPIO_Label=LED7
PA3.Signal=GPIO_Output
PA4.GPIOParameters=GPIO_Label
PA4.GPIO_Label=SPI1_CS
PA4.Signal=GPIO_Output
PA5.Mode=Full_Duplex_Master
PA5.Signal=SPI1_SCK
PA6.Mode=Full_Duplex_Master
PA6.Signal=SPI1_MISO
PA7.Mode=Full_Duplex_Master
PA7.Signal=SPI1_MOSI
PA9.Mode=Asynchronous
PA9.Signal=USART1_TX
PB0.GPIOParameters=GPIO_Label
PB0.GPIO_Label=IRQ
PB0.Signal=GPIO_Input
PB10.GPIOParameters=GPIO_Label
PB10.GPIO_Label=TapeLED_B
PB10.Signal=GPIO_Output
PB12.Mode=FDCAN_Activate
PB12.Signal=FDCAN2_RX
PB13.Mode=FDCAN_Activate
PB13.Signal=FDCAN2_TX
PB14.Mode=Hardware Flow Control (RS485)
PB14.Signal=USART3_DE
PB3\ (JTDO/TRACESWO).Mode=Trace_Asynchronous_SW
PB3\ (JTDO/TRACESWO).Signal=DEBUG_JTDO-SWO
PB4\ (NJTRST).Signal=S_TIM3_CH1
PB5.Signal=S_TIM3_CH2
PB6.Mode=I2C
PB6.Signal=I2C1_SCL
PB7.Mode=I2C
PB7.Signal=I2C1_SDA
PB8.Mode=FDCAN_Activate
PB8.Signal=FDCAN1_RX
PB9.Mode=FDCAN_Activate
PB9.Signal=FDCAN1_TX
PC0.GPIOParameters=GPIO_Label
PC0.GPIO_Label=LED4
PC0.Signal=GPIO_Output
PC10.Mode=Asynchronous
PC10.Signal=USART3_TX
PC11.Mode=Asynchronous
PC11.Signal=USART3_RX
PC12.Mode=Asynchronous
PC12.Signal=UART5_TX
PC13.GPIOParameters=GPIO_Label
PC13.GPIO_Label=LED3
PC13.Signal=GPIO_Output
PC2_C.GPIOParameters=GPIO_Label
PC2_C.GPIO_Label=LED5
PC2_C.Signal=GPIO_Output
PC4.GPIOParameters=GPIO_Label
PC4.GPIO_Label=SYNC0
PC4.Signal=GPIO_Input
PC5.GPIOParameters=GPIO_Label
PC5.GPIO_Label=SYNC1
PC5.Signal=GPIO_Input
PC6.Mode=Asynchronous
PC6.Signal=USART6_TX
PC7.Mode=Asynchronous
PC7.Signal=USART6_RX
PD0.Mode=Asynchronous
PD0.Signal=UART4_RX
PD1.Mode=Asynchronous
PD1.Signal=UART4_TX
PD12.Signal=S_TIM4_CH1
PD13.Signal=S_TIM4_CH2
PD2.Mode=Asynchronous
PD2.Signal=UART5_RX
PD5.Mode=Asynchronous
PD5.Signal=USART2_TX
PD6.Mode=Asynchronous
PD6.Signal=USART2_RX
PE11.Signal=S_TIM1_CH2
PE13.GPIOParameters=GPIO_Label
PE13.GPIO_Label=TapeLED_R
PE13.Signal=GPIO_Output
PE14.GPIOParameters=GPIO_Label
PE14.GPIO_Label=TapeLED_G
PE14.Signal=GPIO_Output
PE4.GPIOParameters=GPIO_Label
PE4.GPIO_Label=LED1
PE4.Signal=GPIO_Output
PE6.GPIOParameters=GPIO_Label
PE6.GPIO_Label=LED2
PE6.Signal=GPIO_Output
PE9.Signal=S_TIM1_CH1
PH0-OSC_IN\ (PH0).Mode=HSE-External-Oscillator
PH0-OSC_IN\ (PH0).Signal=RCC_OSC_IN
PH1-OSC_OUT\ (PH1).Mode=HSE-External-Oscillator
PH1-OSC_OUT\ (PH1).Signal=RCC_OSC_OUT
RCC.HSE_VALUE=32000000
RCC.SYSCLKFreq_VALUE=480000000
RCC.SYSCLKSource=RCC_SYSCLKSOURCE_PLLCLK
board=custom
